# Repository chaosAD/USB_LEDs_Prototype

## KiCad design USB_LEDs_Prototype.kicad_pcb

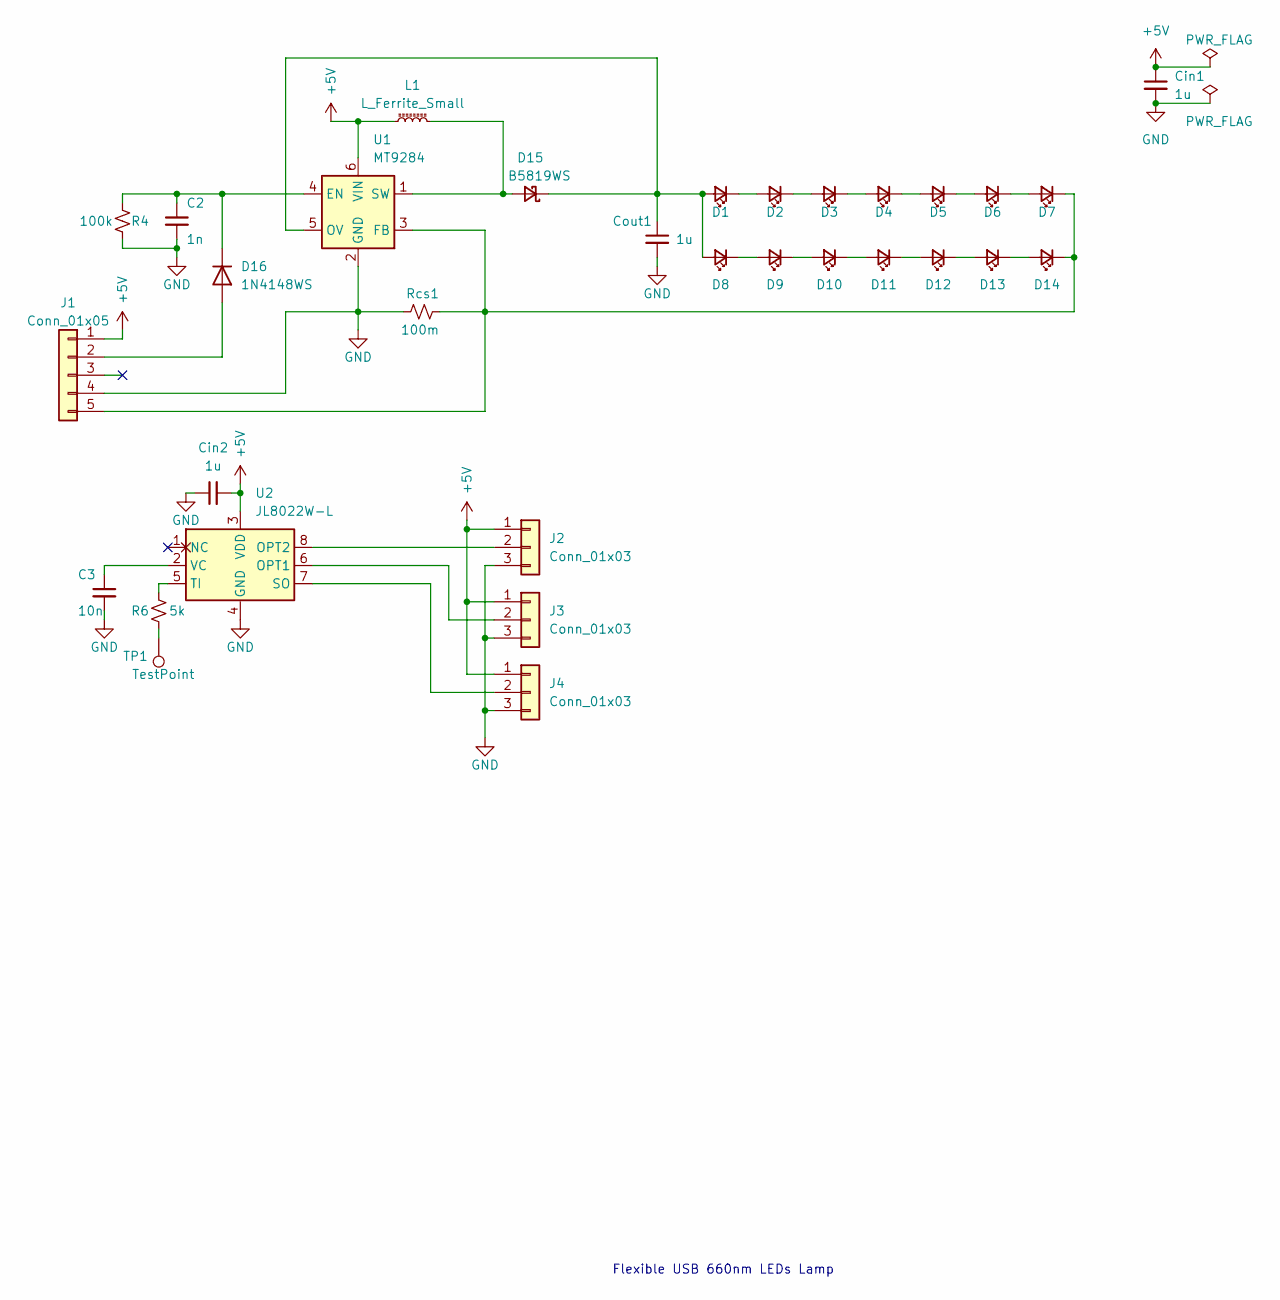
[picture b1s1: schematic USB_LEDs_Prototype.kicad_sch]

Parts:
C2: 1n; C_0603_1608Metric
C3: 10n; C_0603_1608Metric
Cin1, Cin2: 1u; C_0603_1608Metric
Cout1: 1u; C_0603_1608Metric
D1, D2, D3, D4, D5, D6, D7, D8, D9, D10, D11, D12, D13, D14: 660nm; LED_Yuji_5730
D15: B5819WS; D_SOD-323
D16: 1N4148WS; D_SOD-323
J1: Conn_01x05; PinHeader_1x05_P2.54mm_Vertical
J2, J3, J4: Conn_01x03; PinHeader_1x03_P2.54mm_Vertical
L1: L_Ferrite_Small; L_Abracon_ASPI-3012S
R4: 100k; R_Box_L8.4mm_W2.5mm_P5.08mm
R6: 5k; R_0603_1608Metric
Rcs1: 100m; R_0805_2012Metric_Pad1.20x1.40mm_HandSolder
TP1: TestPoint; TestPoint_Loop_D2.50mm_Drill1.0mm
U1: MT9284; SOT-23-6
U2: JL8022W-L; SOIC-8_3.9x4.9mm_P1.27mm

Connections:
+5V: Cin1.1, Cin2.2, J1.1, J2.1, J3.1, J4.1, L1.1, U1.6 (VIN), U2.3 (VDD)
GND: C2.2, C3.2, Cin1.2, Cin2.1, Cout1.2, J1.4, J2.3, J3.3, J4.3, R4.1, Rcs1.1, U1.2 (GND), U2.4 (GND)
unnamed: C2.1, D16.1 (K), R4.2, U1.4 (EN)
unnamed: C3.1, U2.2 (VC)
unnamed: Cout1.1, D1.2 (A), D8.2 (A), D15.1 (K), U1.5 (OV)
unnamed: D1.1 (K), D2.2 (A)
unnamed: D2.1 (K), D3.2 (A)
unnamed: D3.1 (K), D4.2 (A)
unnamed: D4.1 (K), D5.2 (A)
unnamed: D5.1 (K), D6.2 (A)
unnamed: D6.1 (K), D7.2 (A)
unnamed: D8.1 (K), D9.2 (A)
unnamed: D10.1 (K), D11.2 (A)
unnamed: D9.1 (K), D10.2 (A)
unnamed: D11.1 (K), D12.2 (A)
unnamed: D12.1 (K), D13.2 (A)
unnamed: D13.1 (K), D14.2 (A)
unnamed: D7.1 (K), D14.1 (K), J1.5, Rcs1.2, U1.3 (FB)
unnamed: D15.2 (A), L1.2, U1.1 (SW)
unnamed: D16.2 (A), J1.2
unnamed: R6.1, TP1.1
unnamed: R6.2, U2.5 (TI)
unnamed: J3.2, U2.6 (OPT1)
unnamed: J4.2, U2.7 (SO)
unnamed: J2.2, U2.8 (OPT2)

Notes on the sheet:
Flexible USB 660nm LEDs Lamp

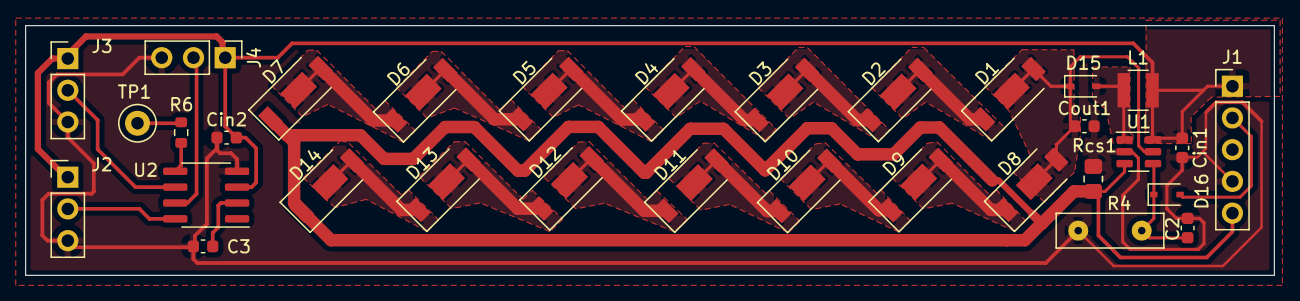
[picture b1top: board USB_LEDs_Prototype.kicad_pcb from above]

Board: 2 copper layers, 100.0 x 20.0 mm, 32 parts (0 on the bottom side), 25 nets.

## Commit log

2022-12-13 The is development of the USB LED prototype
2022-12-13 Ignore *.bak in .gitignore file
